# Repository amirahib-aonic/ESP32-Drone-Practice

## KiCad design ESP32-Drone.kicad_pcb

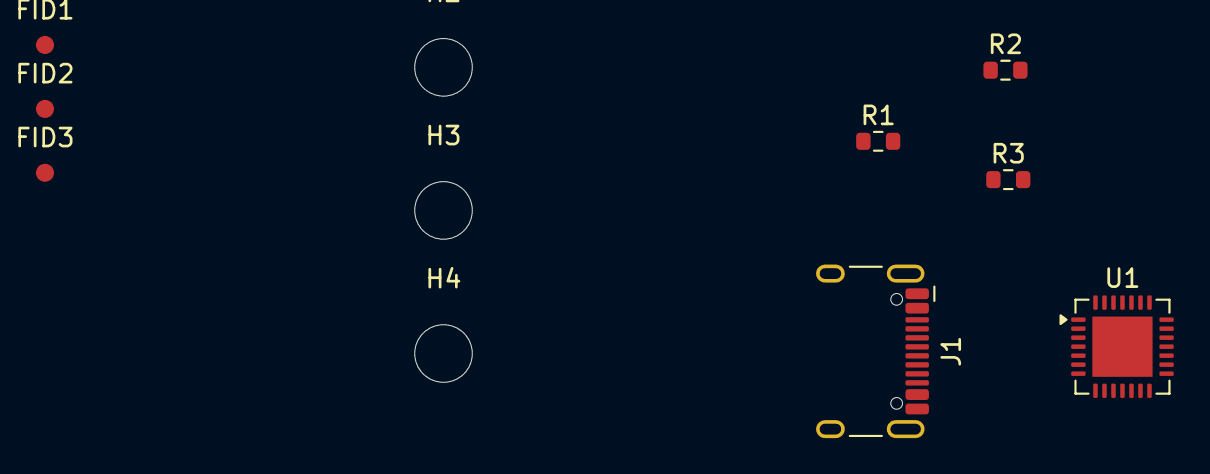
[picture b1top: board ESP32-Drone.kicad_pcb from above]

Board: 2 copper layers, 12 parts (0 on the bottom side), 7 nets, no tracks yet.

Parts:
FID1, FID2, FID3: Fiducial-1mmPad-2mmMask; Fiducial_1mm_Mask2mm
H1, H2, H3, H4: MountingHole; MountingHole_3.2mm_M3
J1: USB_C_Receptacle_USB2.0_16P; USB_C_Receptacle_HCTL_HC-TYPE-C-16P-01A
R1: 100K; R_0603_1608Metric
R2, R3: 5.1K; R_0603_1608Metric
U1: CP2102N-Axx-xQFN28; QFN-28-1EP_5x5mm_P0.5mm_EP3.35x3.35mm

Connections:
+5V: J1.A4 (VBUS), J1.A9 (VBUS), J1.B4 (VBUS), J1.B9 (VBUS), R1.1
/ESP32/USB_DN: J1.A7 (D-), J1.B7 (D-), U1.5 (D-)
/ESP32/USB_DP: J1.A6 (D+), J1.B6 (D+), U1.4 (D+)
/Power Management/CC1: J1.A5 (CC1), R2.1
/Power Management/CC2: J1.B5 (CC2), R3.1
GND: J1.A1 (GND), J1.A12 (GND), J1.B1 (GND), J1.B12 (GND), J1.S1 (SHIELD), R1.2, R2.2, R3.2
unnamed: U1.3 (GND), U1.29 (GND)

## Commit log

2026-01-06 Test branching 1
2026-01-09 Commit ESP 50%
2026-01-09 Just tryna track and commit this backup file
2026-01-09 ESP finished symbol assembly
2026-01-14 All component assembly ready. Pending net classifications
2026-01-14 im ready
2026-02-11 Pre standardising kicad components GitHub run
2026-02-11 First commit test with library test
2026-02-12 I added a flip flop for digikey library test
